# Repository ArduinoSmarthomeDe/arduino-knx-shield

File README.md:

# Arduino Uno KNX TP-UART Shield

## Description

DIY shield for connecting the KNX bus to an Arduino Uno. Uses the first version of the Siemens TP-UART chip, which is very easy to solder by hand. In addition, there are 6 LEDs and 2 buttons on board for test purposes (e.g. for sending and receiving KNX group addresses).

The serial hardware interface (RX / TX), which is also used by the Arduino Uno from the USB port, can simply be separated from the TP-UART chip using a DIP switch. Alternatively, the serial interface of the TP-UART can be switched to software serial pins or is accessed on a connector.

*This is just a DIY board, so there is no official KNX stack to configure via the ETS software.*

**NOTICE: The shield fits best on an Arduino Uno with a micro USB connector. Otherwise it can lead to problems with USB Type A connector.**

## Preview

A little look at the finished circuit board (3D model):

## Parts

Some parts are a hard to come by, so here is a short overview of known distributors (no affiliates).

| Item      | Part                    | Link  |
| --------- |:-----------------------:| ----- |
| U1        | Siemens TP-Uart         | http://www.opternus.com/de/siemens/knx-chipset/knx-transceiver-ics-tp-uart-fze1066.html |
| D2        | P4SMAJ43A               | https://www.reichelt.de/tvs-diode-unidirektional-43-v-400-w-do-214ac-sma-p4smaj43a-p272910.html?&trstct=pos_0&nbc=1 |
| D3        | RND US1M-AT             | https://www.reichelt.de/gleichrichterdiode-1000-v-1-a-do-214ac-sma-us-1m-p146618.html?&trstct=pos_0&nbc=1 |
| KNX Pins  | WAGO 243-131				 | https://www.reichelt.de/wago-loetstifte-fuer-buchsenklemmen-wago-243-131-p67263.html?&trstct=pos_0&nbc=1 |

## Layout & Production 

You can find all the open data here as a [KiCad](http://kicad.github.io) project. You can find all the necessary dependencies such as footprints or libraries in the folder **KiCad Symbols & Footprints**.

The *Gerber files* for the production of the board can be found here under **releases**.

## License

The MIT License (MIT)

Copyright (c) 2021 André Husken hello@arduino-smarthome.de

Permission is hereby granted, free of charge, to any person obtaining a copy of this software and associated documentation files (the "Software"), to deal in the Software without restriction, including without limitation the rights to use, copy, modify, merge, publish, distribute, sublicense, and/or sell copies of the Software, and to permit persons to whom the Software is furnished to do so, subject to the following conditions:

The above copyright notice and this permission notice shall be included in all copies or substantial portions of the Software.

THE SOFTWARE IS PROVIDED "AS IS", WITHOUT WARRANTY OF ANY KIND, EXPRESS OR IMPLIED, INCLUDING BUT NOT LIMITED TO THE WARRANTIES OF MERCHANTABILITY, FITNESS FOR A PARTICULAR PURPOSE AND NONINFRINGEMENT. IN NO EVENT SHALL THE AUTHORS OR COPYRIGHT HOLDERS BE LIABLE FOR ANY CLAIM, DAMAGES OR OTHER LIABILITY, WHETHER IN AN ACTION OF CONTRACT, TORT OR OTHERWISE, ARISING FROM, OUT OF OR IN CONNECTION WITH THE SOFTWARE OR THE USE OR OTHER DEALINGS IN THE SOFTWARE.

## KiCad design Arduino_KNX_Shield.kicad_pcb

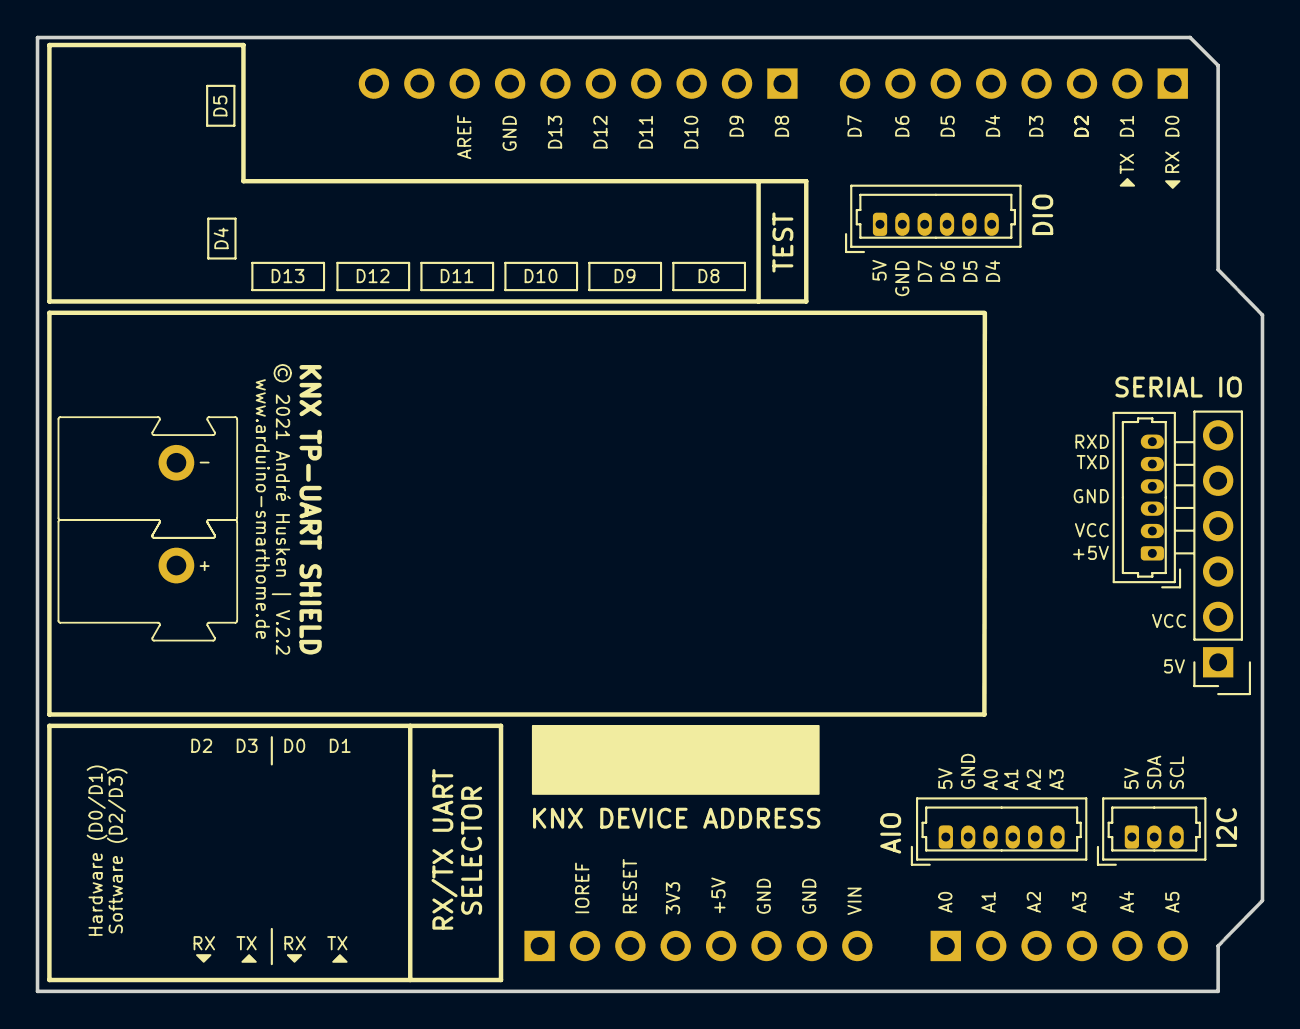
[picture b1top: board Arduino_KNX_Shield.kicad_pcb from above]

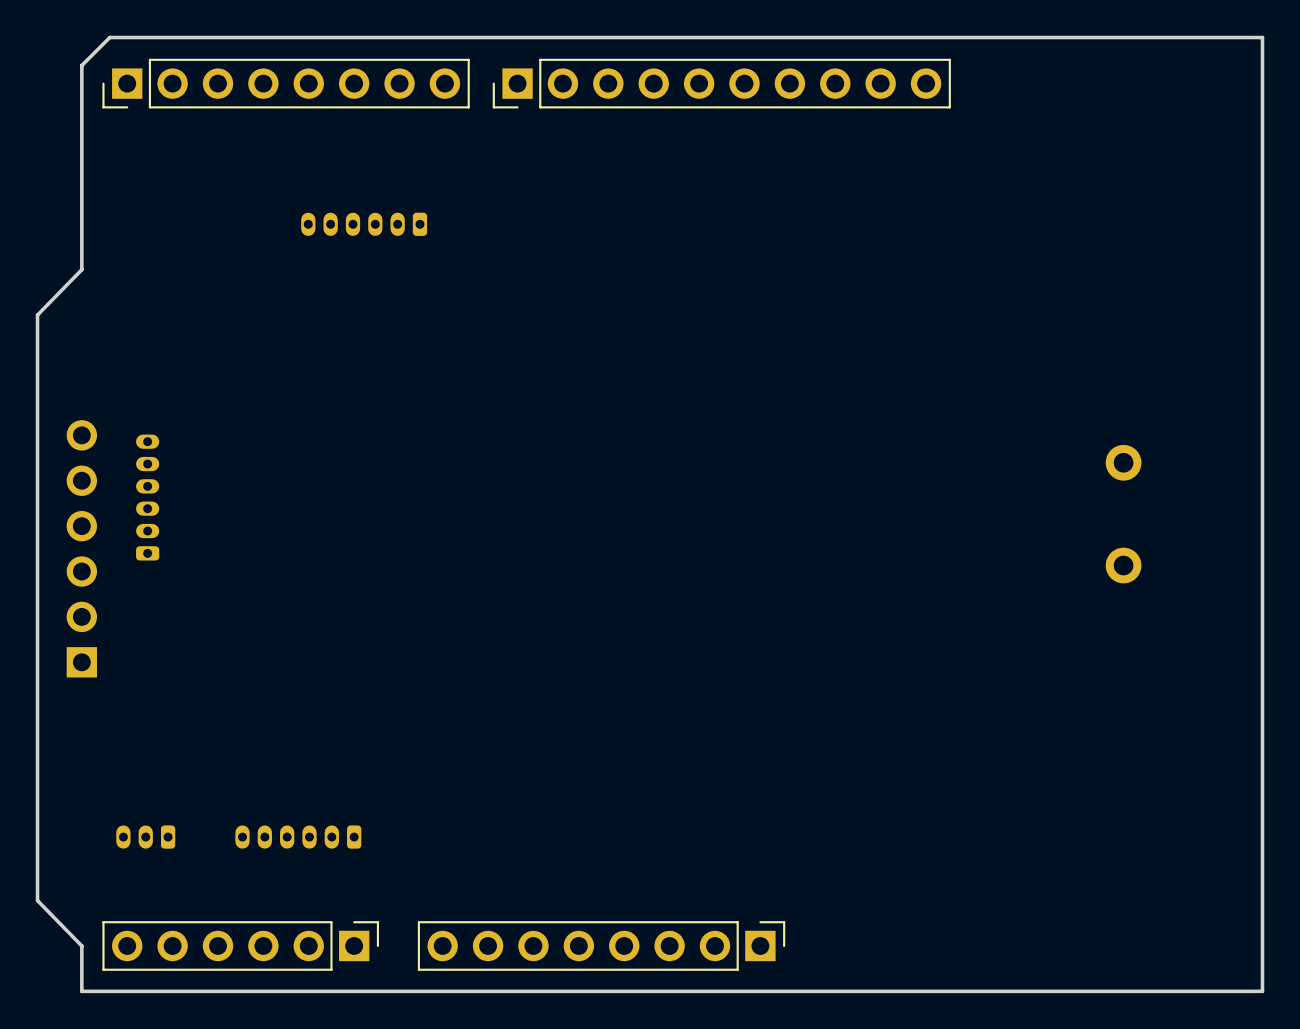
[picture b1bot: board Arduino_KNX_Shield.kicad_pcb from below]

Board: 2 copper layers, 68.5 x 53.4 mm, 10 parts (4 on the bottom side), 15 nets, no tracks yet.

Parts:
J1, J4: Conn_01x08_Male; PinHeader_1x08_P2.54mm_Vertical
J2: Conn_01x10_Male; PinHeader_1x10_P2.54mm_Vertical
J3: Conn_01x06_Male; PinHeader_1x06_P2.54mm_Vertical
J5: KNX; Wago_KNX_243-211_1x02_P5.75mm_Vertical_Top
J6, J8, J10: Conn_01x06_Male; Molex_PicoBlade_53047-0610_1x06_P1.25mm_Vertical
J7: Conn_01x06_Male; PinSocket_1x06_P2.54mm_Vertical
J9: Conn_01x03_Male; Molex_PicoBlade_53047-0310_1x03_P1.25mm_Vertical

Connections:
+5V: J4.5, J6.1, J7.1, J8.1, J9.1, J10.1
A0: J3.1, J10.3
A1: J3.2, J10.4
A2: J3.3, J10.5
A3: J3.4, J10.6
A4: J3.5, J9.2
A5: J3.6, J9.3
D4: J1.5, J8.6
D5: J1.6, J8.5
D6: J1.7, J8.4
D7: J1.8, J8.3
GND: J2.7, J4.6, J4.7, J6.3, J6.4, J7.3, J7.4, J8.2, J10.2
RXD: J6.6, J7.6
TXD: J6.5, J7.5
VCC: J6.2, J7.2

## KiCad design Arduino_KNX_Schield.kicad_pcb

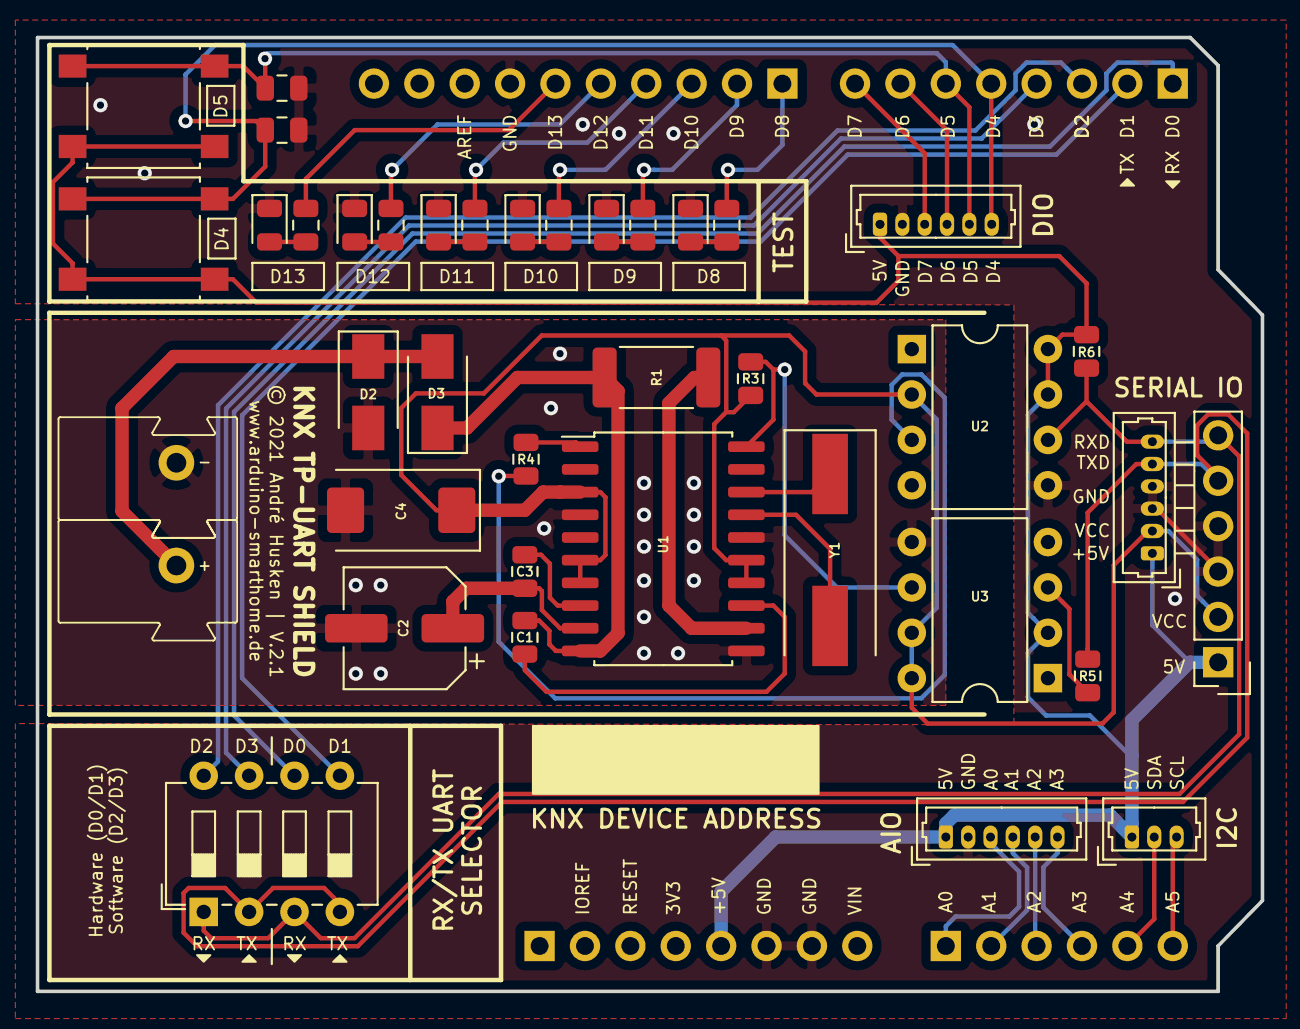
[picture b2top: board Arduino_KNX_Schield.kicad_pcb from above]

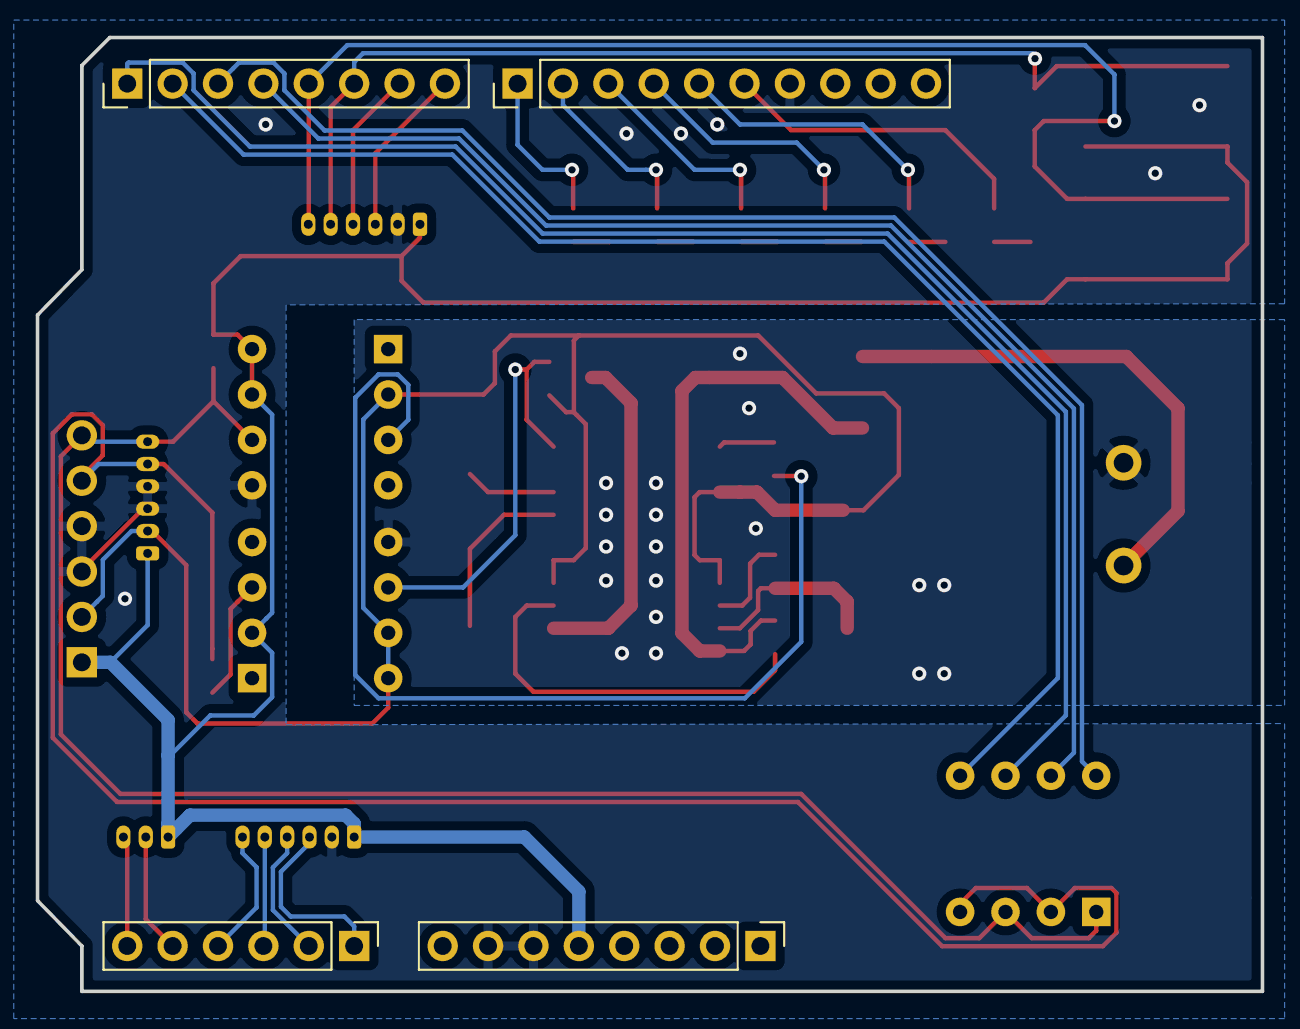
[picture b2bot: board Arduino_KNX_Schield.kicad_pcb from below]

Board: 2 copper layers, 68.5 x 53.4 mm, 42 parts (4 on the bottom side), 44 nets.

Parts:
C1, C3: 47nF; C_0805_2012Metric
C2: 100uF/35V; CP_Elec_6.3x7.7
C4: T491D 6,8U 35; CP_EIA-7343-20_Kemet-V
D1, D4, D5, D6, D7, D8: LED; LED_0805_2012Metric
D2: P4SMAJ43A; D_SMA
D3: RND US1M-AT; D_SMA
J1, J4: Conn_01x08_Male; PinHeader_1x08_P2.54mm_Vertical
J2: Conn_01x10_Male; PinHeader_1x10_P2.54mm_Vertical
J3: Conn_01x06_Male; PinHeader_1x06_P2.54mm_Vertical
J5: KNX; Wago_KNX_243-211_1x02_P5.75mm_Vertical_Top
J6, J8, J10: Conn_01x06_Male; Molex_PicoBlade_53047-0610_1x06_P1.25mm_Vertical
J7: Conn_01x06_Male; PinSocket_1x06_P2.54mm_Vertical
J9: Conn_01x03_Male; Molex_PicoBlade_53047-0310_1x03_P1.25mm_Vertical
R1: 68/1W; R_2512_6332Metric
R2, R7, R8, R9, R10, R11: 1K; R_0805_2012Metric
R3, R6, R12, R13: 10K; R_0805_2012Metric
R4, R5: 820; R_0805_2012Metric
SW1: SW_DIP_x04; SW_DIP_SPSTx04_Slide_6.7x11.72mm_W7.62mm_P2.54mm_LowProfile
SW2, SW3: SW_Push; SW_SPST_B3S-1000
U1: EIB-TP-UART; SOIC-20W_7.5x12.8mm_P1.27mm
U2, U3: 6N137; DIP-8_W7.62mm
Y1: 4.915MHz; Crystal_SMD_HC49-SD

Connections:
+5V: J4.5, J6.1, J7.1, J8.1, J9.1, J10.1, R6.2, SW2.2, SW3.2, U2.7, U2.8, U3.2
A0: J3.1, J10.3
A1: J3.2, J10.4
A2: J3.3, J10.5
A3: J3.4, J10.6
A4: J3.5, J9.2
A5: J3.6, J9.3
D0: J1.1, SW1.6
D1: J1.2, SW1.5
D2: J1.3, SW1.8
D3: J1.4, SW1.7
D4: J1.5, J8.6, R12.1, SW2.1
D5: J1.6, J8.5, R13.1, SW3.1
D6: J1.7, J8.4
D7: J1.8, J8.3
D8: J2.1, R11.2
D9: J2.2, R10.2
D10: J2.3, R9.2
D11: J2.4, R8.2
D12: J2.5, R7.2
D13: J2.6, R2.2
GND: D1.1, D4.1, D5.1, D6.1, D7.1, D8.1, J2.7, J4.6, J4.7, J6.3, J6.4, J7.3, J7.4, J8.2, J10.2, R12.2, R13.2, U2.5
KNX+: D2.1, D3.2, J5.1
KNX-: C2.2, C4.2, D2.2, J5.2, U1.4, U1.11, U1.16, U3.5
unnamed: C1.1, D3.1, R1.1, U1.10
unnamed: C1.2, U1.13
unnamed: C2.1, C3.1, U1.9
unnamed: C3.2, U1.8
unnamed: D1.2, R2.1
unnamed: D4.2, R7.1
unnamed: D5.2, R8.1
unnamed: D6.2, R9.1
unnamed: D7.2, R10.1
unnamed: D8.2, R11.1
unnamed: R1.2, U1.12
unnamed: R3.1, U1.20, U3.6
unnamed: R4.1, U2.3
unnamed: R4.2, U1.1
unnamed: R5.2, U3.3
unnamed: U1.17, Y1.2
unnamed: U1.18, Y1.1
RXD: J6.6, J7.6, R6.1, SW1.1, SW1.3, U2.6
TXD: J6.5, J7.5, R5.1, SW1.2, SW1.4
VCC: C4.1, J6.2, J7.2, R3.2, U1.3, U1.6, U1.7, U1.14, U1.15, U2.2, U3.7, U3.8

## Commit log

2021-09-07 gitignore
2021-09-07 preview
2021-09-07 KiCad dependencies
2021-09-07 V.2.1
2021-09-07 Readme
2021-09-08 V.2.2
2021-09-08 readme, preview

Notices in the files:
Arduino_KNX_Schield.kicad_pcb:
© 2021 André Husken | V.2.1
Arduino_KNX_Shield.kicad_pcb:
© 2021 André Husken | V.2.2
